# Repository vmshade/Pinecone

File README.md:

# Pinecone - An RP2040 powered dev board
#### What is it?
Pinecone is an RP2040 powered dev board, inspired by the legendary Arduino Uno line-up. It features things like a USB-C port which the Unos simply lack.
#### Why?
I created this to jump-start and expand my hobby in electronics by designing and hopefully manufacturing my first PCB. I also previously used the Uno R3, and thought there are alot of things i could do to improve it, while making it smaller.

### Here are some cool features Pinecone has
- RP2040
- 16MB of fast, QSPI Flash
- USB-C
- 29 GPIOs broken out into easy to use sockets
- Neopixel
- Power-On LED
- ESD and Voltage spike protection
- Small, 5cm x 5cm pcb size

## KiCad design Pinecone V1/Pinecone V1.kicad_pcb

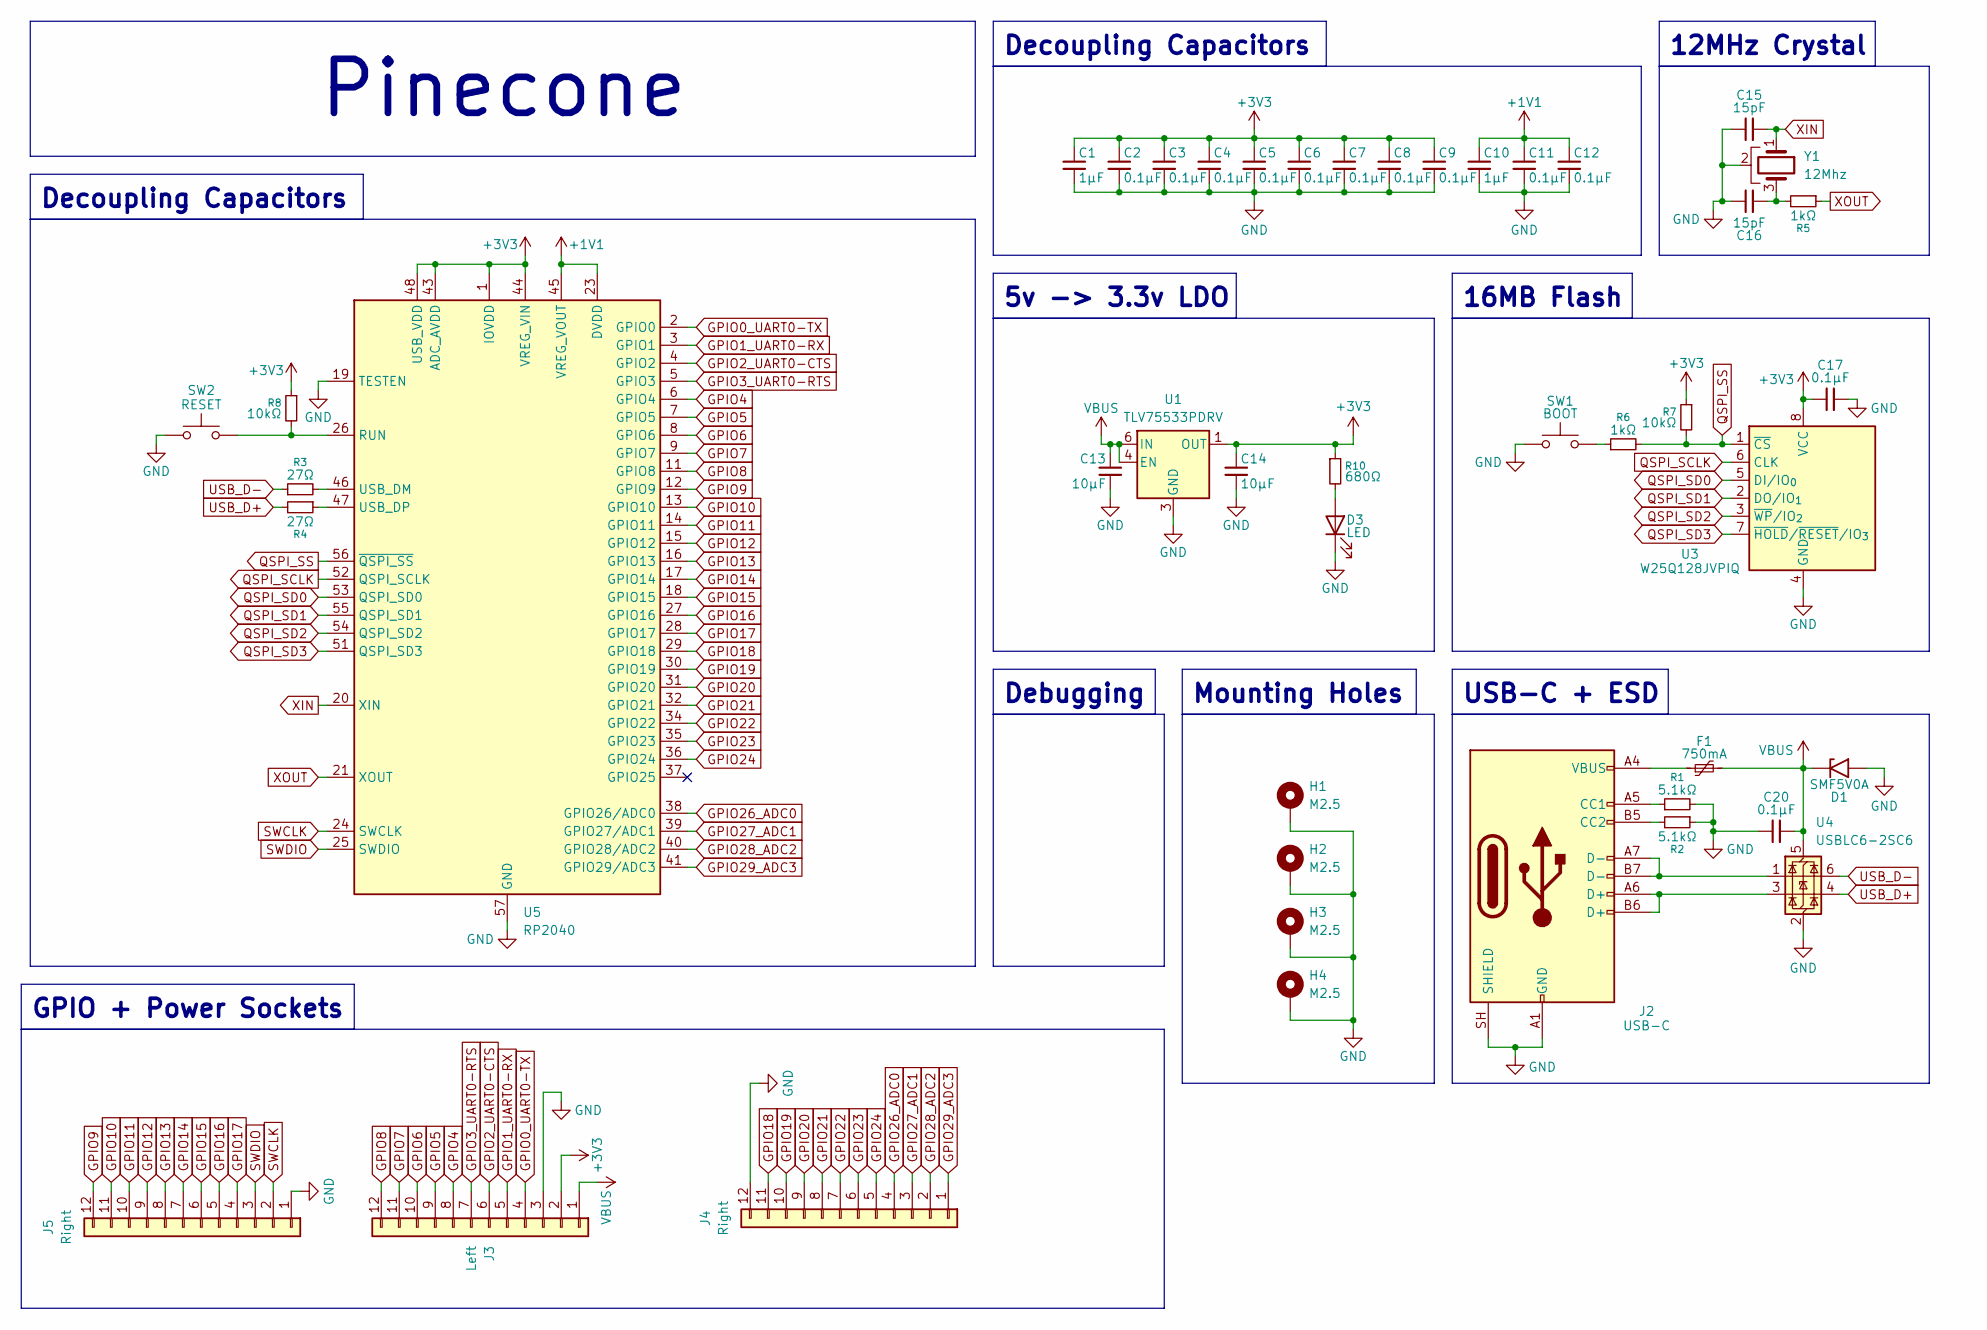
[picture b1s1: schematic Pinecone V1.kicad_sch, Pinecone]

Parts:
C1, C10: 1µF; C_0402_1005Metric
C2, C3, C4, C5, C6, C7, C8, C9, C11, C12, C17, C20: 0.1µF; C_0402_1005Metric
C13, C14: 10µF; C_0603_1608Metric
C15, C16: 15pF; C_0402_1005Metric
D1: SMF5V0A; D_SMF
D3: LED; LED_0805_2012Metric
F1: 750mA; Fuse_1206_3216Metric
H1, H2, H3, H4: M2.5; MountingHole_2.7mm_M2.5_Pad
J2: USB-C; USB_C_Receptacle_HRO_TYPE-C-31-M-12
J3: Left; PinSocket_1x12_P2.54mm_Vertical
J4, J5: Right; PinSocket_1x12_P2.54mm_Vertical_F
R1, R2: 5.1kΩ; R_0402_1005Metric
R3, R4: 27Ω; R_0402_1005Metric
R5, R6: 1kΩ; R_0402_1005Metric
R7, R8: 10kΩ; R_0402_1005Metric
R10: 680Ω; R_0402_1005Metric
SW1: BOOT; SW_PUSH_6mm
SW2: RESET; SW_PUSH_6mm
U1: TLV75533PDRV; WSON-6-1EP_2x2mm_P0.65mm_EP1x1.6mm
U3: W25Q128JVPIQ; WSON-8-1EP_6x5mm_P1.27mm_EP3.4x4.3mm
U4: USBLC6-2SC6; SOT-23-6
U5: RP2040; QFN-56-1EP_7x7mm_P0.4mm_EP3.2x3.2mm
Y1: 12Mhz; Crystal_SMD_3225-4Pin_3.2x2.5mm

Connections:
+1V1: C10.1, C11.1, C12.1, U5.23 (DVDD), U5.45 (VREG_VOUT), U5.50 (DVDD)
+3V3: C1.1, C2.1, C3.1, C4.1, C5.1, C6.1, C7.1, C8.1, C9.1, C14.1, C17.1, J3.2, R7.1, R8.1, R10.1, U1.1 (OUT), U3.8 (VCC), U5.1 (IOVDD), U5.10 (IOVDD), U5.22 (IOVDD), U5.33 (IOVDD), U5.42 (IOVDD), U5.43 (ADC_AVDD), U5.44 (VREG_VIN), U5.48 (USB_VDD), U5.49 (IOVDD)
GND: C1.2, C2.2, C3.2, C4.2, C5.2, C6.2, C7.2, C8.2, C9.2, C10.2, C11.2, C12.2, C13.2, C14.2, C15.1, C16.2, C17.2, C20.1, D1.2 (A2), D3.1 (K), H1.1 (1_1), H2.1 (1_1), H3.1 (1_1), H4.1 (1_1), J2.A1 (GND), J2.A12 (GND), J2.B1 (GND), J2.B12 (GND), J2.SH (SHIELD), J3.3, J4.12, J5.1, R1.2, R2.1, SW1.1, SW2.1, U1.3 (GND), U1.7 (GND), U3.4 (GND), U4.2 (GND), U5.19 (TESTEN), U5.57 (GND), Y1.2; also elsewhere on the board
GPIO0_UART0-TX: J3.4, U5.2 (GPIO0)
GPIO1_UART0-RX: J3.5, U5.3 (GPIO1)
GPIO2_UART0-CTS: J3.6, U5.4 (GPIO2)
GPIO3_UART0-RTS: J3.7, U5.5 (GPIO3)
GPIO4: J3.8, U5.6 (GPIO4)
GPIO5: J3.9, U5.7 (GPIO5)
GPIO6: J3.10, U5.8 (GPIO6)
GPIO7: J3.11, U5.9 (GPIO7)
GPIO8: J3.12, U5.11 (GPIO8)
GPIO9: J5.12, U5.12 (GPIO9)
GPIO10: J5.11, U5.13 (GPIO10)
GPIO11: J5.10, U5.14 (GPIO11)
GPIO12: J5.9, U5.15 (GPIO12)
GPIO13: J5.8, U5.16 (GPIO13)
GPIO14: J5.7, U5.17 (GPIO14)
GPIO15: J5.6, U5.18 (GPIO15)
GPIO16: J5.5, U5.27 (GPIO16)
GPIO17: J5.4, U5.28 (GPIO17)
GPIO18: J4.11, U5.29 (GPIO18)
GPIO19: J4.10, U5.30 (GPIO19)
GPIO20: J4.9, U5.31 (GPIO20)
GPIO21: J4.8, U5.32 (GPIO21)
GPIO22: J4.7, U5.34 (GPIO22)
GPIO23: J4.6, U5.35 (GPIO23)
GPIO24: J4.5, U5.36 (GPIO24)
GPIO26_ADC0: J4.4, U5.38 (GPIO26/ADC0)
GPIO27_ADC1: J4.3, U5.39 (GPIO27/ADC1)
GPIO28_ADC2: J4.2, U5.40 (GPIO28/ADC2)
GPIO29_ADC3: J4.1, U5.41 (GPIO29/ADC3)
NeoPixel: U5.37 (GPIO25)
unnamed: C16.1, R5.2, Y1.3
unnamed: D3.2 (A), R10.2
unnamed: F1.1, J2.A4 (VBUS), J2.A9 (VBUS), J2.B4 (VBUS), J2.B9 (VBUS)
unnamed: J2.A5 (CC1), R1.1
unnamed: J2.B5 (CC2), R2.2
unnamed: J2.A6 (D+), J2.B6 (D+), U4.3 (I/O2)
unnamed: J2.A7 (D-), J2.B7 (D-), U4.1 (I/O1)
unnamed 40: R6.1, SW1.2; also elsewhere on the board
unnamed 41: R8.2, SW2.2, U5.26 (RUN); also elsewhere on the board
unnamed: R3.2, U5.46 (USB_DM)
unnamed: R4.1, U5.47 (USB_DP)
QSPI_SCLK: U3.6 (CLK), U5.52 (QSPI_SCLK)
QSPI_SD0: U3.5 (DI/IO_{0}), U5.53 (QSPI_SD0)
QSPI_SD1: U3.2 (DO/IO_{1}), U5.55 (QSPI_SD1)
QSPI_SD2: U3.3 (~WP/IO_{2}), U5.54 (QSPI_SD2)
QSPI_SD3: U3.7 (~HOLD/~RESET/IO_{3}), U5.51 (QSPI_SD3)
QSPI_SS: R6.2, R7.2, U3.1 (~CS), U5.56 (~QSPI_SS)
SWCLK: J5.2, U5.24 (SWCLK)
SWDIO: J5.3, U5.25 (SWDIO)
USB_D+: R4.2, U4.4 (I/O2)
USB_D-: R3.1, U4.6 (I/O1)
VBUS: C13.1, C20.2, D1.1 (A1), F1.2, J3.1, U1.4 (EN), U1.6 (IN), U4.5 (VBUS)
XIN: C15.2, U5.20 (XIN), Y1.1
XOUT: R5.1, U5.21 (XOUT)

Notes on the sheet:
12MHz Crystal
5v -> 3.3v LDO
Decoupling Capacitors
Pinecone
Mounting Holes
GPIO + Power Sockets
16MB Flash
USB-C + ESD
Debugging

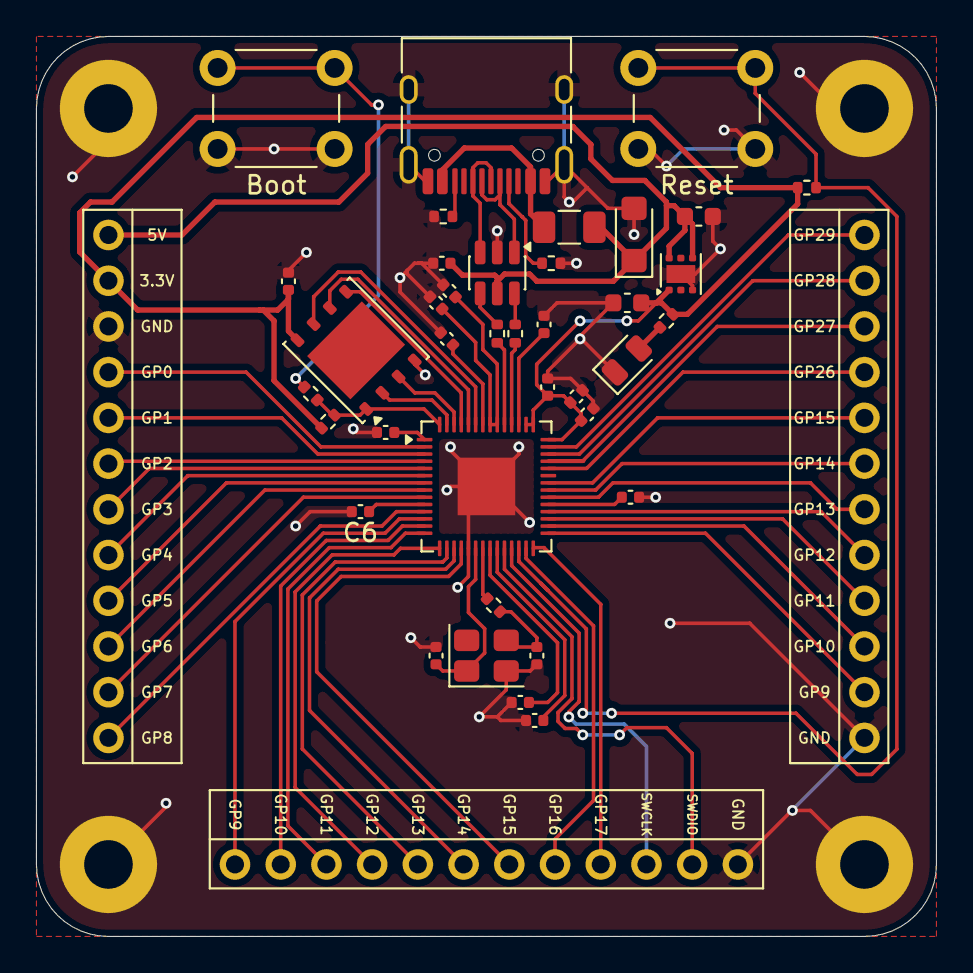
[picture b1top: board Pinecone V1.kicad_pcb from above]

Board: 2 copper layers, 50.0 x 50.0 mm, 45 parts (0 on the bottom side), 56 nets.

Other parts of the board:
Boot: BOOT; SW_PUSH_6mm
Reset: RESET; SW_PUSH_6mm

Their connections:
GND: Boot.1, Reset.1; also elsewhere on the board
unnamed 40: Boot.2; also elsewhere on the board
unnamed 41: Reset.2; also elsewhere on the board

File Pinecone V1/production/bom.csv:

Designator,Footprint,Quantity,Value,LCSC Part #
BOOT,SW_PUSH_6mm,1,BOOT,
"C1, C10",0402,2,1µF,
"C11, C12, C17, C2, C20, C3, C4, C5, C6, C7, C8, C9",0402,12,0.1µF,
"C13, C14",0603,2,10µF,
"C15, C16",0402,2,15pF,
D1,D_SMF,1,SMF5V0A,
D3,0805,1,LED,
F1,1206,1,750mA,
J2,USB_C_Receptacle_HRO_TYPE-C-31-M-12,1,USB-C,
J3,PinSocket_1x12_P2.54mm_Vertical,1,Left,
"J4, J5",PinSocket_1x12_P2.54mm_Vertical_F,2,Right,
"R1, R2",0402,2,5.1kΩ,
R10,0402,1,680kΩ,
"R3, R4",0402,2,27Ω,
"R5, R6",0402,2,1kΩ,
"R7, R8",0402,2,10kΩ,
RESET,SW_PUSH_6mm,1,RESET,
U1,WSON-6-1EP_2x2mm_P0.65mm_EP1x1.6mm,1,TLV75533PDRV,
U3,WSON-8-1EP_6x5mm_P1.27mm_EP3.4x4.3mm,1,W25Q128JVPIQ,
U4,SOT-23-6,1,USBLC6-2SC6,
U5,QFN-56-1EP_7x7mm_P0.4mm_EP3.2x3.2mm,1,RP2040,
Y1,Crystal_SMD_3225-4Pin_3.2x2.5mm,1,12Mhz,
